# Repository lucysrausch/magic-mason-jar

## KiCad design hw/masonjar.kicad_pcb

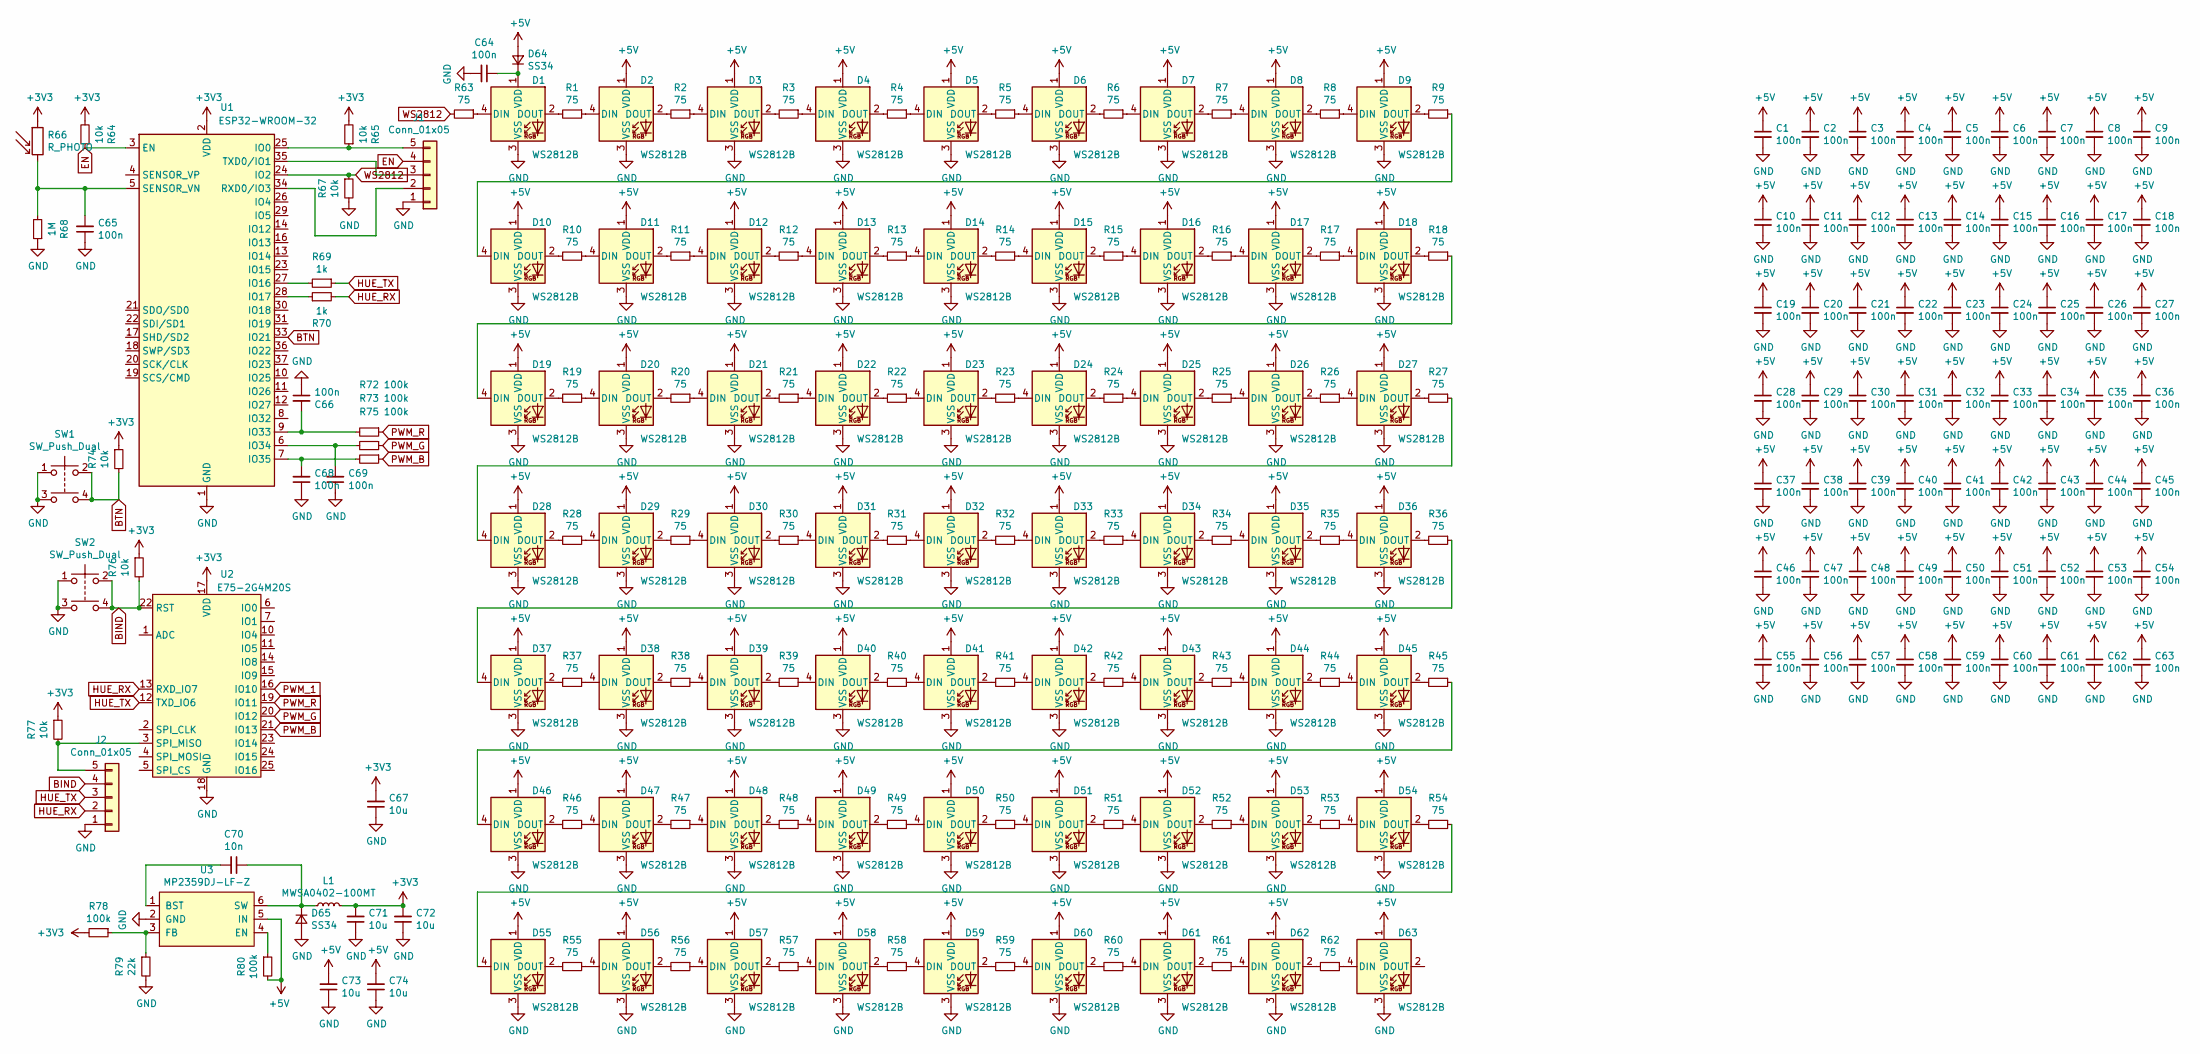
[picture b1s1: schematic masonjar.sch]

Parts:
C1, C2, C3, C4, C5, C6, C7, C8, C9, C10, C11, C12, C13, C14, C15, C16, C17, C18, C19, C20, C21, C22, C23, C24, C25, C26, C27, C28, C29, C30, C31, C32, C33, C34, C35, C36, C37, C38, C39, C40, C41, C42, C43, C44, C45, C46, C47, C48, C49, C50, C51, C52, C53, C54, C55, C56, C57, C58, C59, C60, C61, C62, C63, C64, C65, C66, C68, C69: 100n; C_0402_1005Metric
C67, C71, C72, C73, C74: 10u; C_0805_2012Metric
C70: 10n; C_0603_1608Metric
D1, D2, D3, D4, D5, D6, D7, D8, D9, D10, D11, D12, D13, D14, D15, D16, D17, D18, D19, D20, D21, D22, D23, D24, D25, D26, D27, D28, D29, D30, D31, D32, D33, D34, D35, D36, D37, D38, D39, D40, D41, D42, D43, D44, D45, D46, D47, D48, D49, D50, D51, D52, D53, D54, D55, D56, D57, D58, D59, D60, D61, D62, D63: WS2812B; WS2812D
D64, D65: SS34; D_SMA
J1, J2: Conn_01x05; PinHeader_1x05_P2.54mm_Vertical
L1: MWSA0402-100MT; L_Taiyo-Yuden_MD-4040
R1, R2, R3, R4, R5, R6, R7, R8, R9, R10, R11, R12, R13, R14, R15, R16, R17, R18, R19, R20, R21, R22, R23, R24, R25, R26, R27, R28, R29, R30, R31, R32, R33, R34, R35, R36, R37, R38, R39, R40, R41, R42, R43, R44, R45, R46, R47, R48, R49, R50, R51, R52, R53, R54, R55, R56, R57, R58, R59, R60, R61, R62, R63: 75; R_0402_1005Metric
R64, R65, R67, R74, R76, R77: 10k; R_0402_1005Metric
R66: R_PHOTO; LED_0805_2012Metric
R68: 1M; R_0402_1005Metric
R69, R70: 1k; R_0402_1005Metric
R72, R73, R75, R78, R80: 100k; R_0402_1005Metric
R79: 22k; R_0402_1005Metric
SW1, SW2: SW_Push_Dual; SW_Push_1P1T_NO_6x6mm_H9.5mm
U1: ESP32-WROOM-32
U2: E75-2G4M20S; E75-2G4M10S
U3: MP2359DJ-LF-Z_[C14259]; SOT-23-6

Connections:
+3V3: C67.2, C71.2, C72.2, L1.2, R64.2, R65.2, R66.1, R74.1, R76.1, R77.1, R78.2, U1.2 (VDD), U2.17 (VDD)
+5V: C1.1, C2.1, C3.1, C4.1, C5.1, C6.1, C7.1, C8.1, C9.1, C10.1, C11.1, C12.1, C13.1, C14.1, C15.1, C16.1, C17.1, C18.1, C19.1, C20.1, C21.1, C22.1, C23.1, C24.1, C25.1, C26.1, C27.1, C28.1, C29.1, C30.1, C31.1, C32.1, C33.1, C34.1, C35.1, C36.1, C37.1, C38.1, C39.1, C40.1, C41.1, C42.1, C43.1, C44.1, C45.1, C46.1, C47.1, C48.1, C49.1, C50.1, C51.1, C52.1, C53.1, C54.1, C55.1, C56.1, C57.1, C58.1, C59.1, C60.1, C61.1, C62.1, C63.1, C73.2, C74.2, D2.1 (VDD), D3.1 (VDD), D4.1 (VDD), D5.1 (VDD), D6.1 (VDD), D7.1 (VDD), D8.1 (VDD), D9.1 (VDD), D10.1 (VDD), D11.1 (VDD), D12.1 (VDD), D13.1 (VDD), D14.1 (VDD), D15.1 (VDD), D16.1 (VDD), D17.1 (VDD), D18.1 (VDD), D19.1 (VDD), D20.1 (VDD), D21.1 (VDD), D22.1 (VDD), D23.1 (VDD), D24.1 (VDD), D25.1 (VDD), D26.1 (VDD), D27.1 (VDD), D28.1 (VDD), D29.1 (VDD), D30.1 (VDD), D31.1 (VDD), D32.1 (VDD), D33.1 (VDD), D34.1 (VDD), D35.1 (VDD), D36.1 (VDD), D37.1 (VDD), D38.1 (VDD), D39.1 (VDD), D40.1 (VDD), D41.1 (VDD), D42.1 (VDD), D43.1 (VDD), D44.1 (VDD), D45.1 (VDD), D46.1 (VDD), D47.1 (VDD), D48.1 (VDD), D49.1 (VDD), D50.1 (VDD), D51.1 (VDD), D52.1 (VDD), D53.1 (VDD), D54.1 (VDD), D55.1 (VDD), D56.1 (VDD), D57.1 (VDD), D58.1 (VDD), D59.1 (VDD), D60.1 (VDD), D61.1 (VDD), D62.1 (VDD), D63.1 (VDD), D64.2 (A), R80.2, U3.5 (IN)
BIND: J2.4, R76.2, SW2.2, SW2.4, U2.22 (RST)
BTN: R74.2, SW1.2, SW1.4, U1.33 (IO21)
EN: J1.4, R64.1, U1.3 (EN)
GND: C1.2, C2.2, C3.2, C4.2, C5.2, C6.2, C7.2, C8.2, C9.2, C10.2, C11.2, C12.2, C13.2, C14.2, C15.2, C16.2, C17.2, C18.2, C19.2, C20.2, C21.2, C22.2, C23.2, C24.2, C25.2, C26.2, C27.2, C28.2, C29.2, C30.2, C31.2, C32.2, C33.2, C34.2, C35.2, C36.2, C37.2, C38.2, C39.2, C40.2, C41.2, C42.2, C43.2, C44.2, C45.2, C46.2, C47.2, C48.2, C49.2, C50.2, C51.2, C52.2, C53.2, C54.2, C55.2, C56.2, C57.2, C58.2, C59.2, C60.2, C61.2, C62.2, C63.2, C64.2, C65.1, C66.1, C67.1, C68.1, C69.1, C71.1, C72.1, C73.1, C74.1, D1.3 (VSS), D2.3 (VSS), D3.3 (VSS), D4.3 (VSS), D5.3 (VSS), D6.3 (VSS), D7.3 (VSS), D8.3 (VSS), D9.3 (VSS), D10.3 (VSS), D11.3 (VSS), D12.3 (VSS), D13.3 (VSS), D14.3 (VSS), D15.3 (VSS), D16.3 (VSS), D17.3 (VSS), D18.3 (VSS), D19.3 (VSS), D20.3 (VSS), D21.3 (VSS), D22.3 (VSS), D23.3 (VSS), D24.3 (VSS), D25.3 (VSS), D26.3 (VSS), D27.3 (VSS), D28.3 (VSS), D29.3 (VSS), D30.3 (VSS), D31.3 (VSS), D32.3 (VSS), D33.3 (VSS), D34.3 (VSS), D35.3 (VSS), D36.3 (VSS), D37.3 (VSS), D38.3 (VSS), D39.3 (VSS), D40.3 (VSS), D41.3 (VSS), D42.3 (VSS), D43.3 (VSS), D44.3 (VSS), D45.3 (VSS), D46.3 (VSS), D47.3 (VSS), D48.3 (VSS), D49.3 (VSS), D50.3 (VSS), D51.3 (VSS), D52.3 (VSS), D53.3 (VSS), D54.3 (VSS), D55.3 (VSS), D56.3 (VSS), D57.3 (VSS), D58.3 (VSS), D59.3 (VSS), D60.3 (VSS), D61.3 (VSS), D62.3 (VSS), D63.3 (VSS), D65.2 (A), J1.1, J2.1, R67.2, R68.1, R79.2, SW1.1, SW1.3, SW2.1, SW2.3, U1.1 (GND), U1.15 (GND), U1.38 (GND), U1.39, U2.18 (GND), U3.2 (GND)
HUE_RX: J2.2, R70.2, U2.13 (RXD_IO7)
HUE_TX: J2.3, R69.1, U2.12 (TXD_IO6)
unnamed: C64.1, D1.1 (VDD), D64.1 (K)
unnamed: C65.2, R66.2, R68.2, U1.5 (SENSOR_VN)
unnamed: C66.2, R72.2, U1.9 (IO33)
unnamed: C68.2, R75.2, U1.7 (IO35)
unnamed: C69.2, R73.2, U1.6 (IO34)
unnamed: C70.1, D65.1 (K), L1.1, U3.6 (SW)
unnamed: C70.2, U3.1 (BST)
unnamed: D1.2 (DOUT), R1.2
unnamed: D1.4 (DIN), R63.1
unnamed: D2.2 (DOUT), R2.2
unnamed: D2.4 (DIN), R1.1
unnamed: D3.2 (DOUT), R3.2
unnamed: D3.4 (DIN), R2.1
unnamed: D4.2 (DOUT), R4.2
unnamed: D4.4 (DIN), R3.1
unnamed: D5.2 (DOUT), R5.2
unnamed: D5.4 (DIN), R4.1
unnamed: D6.2 (DOUT), R6.2
unnamed: D6.4 (DIN), R5.1
unnamed: D7.2 (DOUT), R7.2
unnamed: D7.4 (DIN), R6.1
unnamed: D8.2 (DOUT), R8.2
unnamed: D8.4 (DIN), R7.1
unnamed: D9.2 (DOUT), R9.2
unnamed: D9.4 (DIN), R8.1
unnamed: D10.2 (DOUT), R10.2
unnamed: D10.4 (DIN), R9.1
unnamed: D11.2 (DOUT), R11.2
unnamed: D11.4 (DIN), R10.1
unnamed: D12.2 (DOUT), R12.2
unnamed: D12.4 (DIN), R11.1
unnamed: D13.2 (DOUT), R13.2
unnamed: D13.4 (DIN), R12.1
unnamed: D14.2 (DOUT), R14.2
unnamed: D14.4 (DIN), R13.1
unnamed: D15.2 (DOUT), R15.2
unnamed: D15.4 (DIN), R14.1
unnamed: D16.2 (DOUT), R16.2
unnamed: D16.4 (DIN), R15.1
unnamed: D17.2 (DOUT), R17.2
unnamed: D17.4 (DIN), R16.1
unnamed: D18.2 (DOUT), R18.2
unnamed: D18.4 (DIN), R17.1
unnamed: D19.2 (DOUT), R19.2
unnamed: D19.4 (DIN), R18.1
unnamed: D20.2 (DOUT), R20.2
unnamed: D20.4 (DIN), R19.1
unnamed: D21.2 (DOUT), R21.2
unnamed: D21.4 (DIN), R20.1
unnamed: D22.2 (DOUT), R22.2
unnamed: D22.4 (DIN), R21.1
unnamed: D23.2 (DOUT), R23.2
unnamed: D23.4 (DIN), R22.1
unnamed: D24.2 (DOUT), R24.2
unnamed: D24.4 (DIN), R23.1
unnamed: D25.2 (DOUT), R25.2
unnamed: D25.4 (DIN), R24.1
unnamed: D26.2 (DOUT), R26.2
unnamed: D26.4 (DIN), R25.1
unnamed: D27.2 (DOUT), R27.2
unnamed: D27.4 (DIN), R26.1
unnamed: D28.2 (DOUT), R28.2
unnamed: D28.4 (DIN), R27.1
unnamed: D29.2 (DOUT), R29.2
unnamed: D29.4 (DIN), R28.1
unnamed: D30.2 (DOUT), R30.2
unnamed: D30.4 (DIN), R29.1
unnamed: D31.2 (DOUT), R31.2
unnamed: D31.4 (DIN), R30.1
unnamed: D32.2 (DOUT), R32.2
unnamed: D32.4 (DIN), R31.1
unnamed: D33.2 (DOUT), R33.2
unnamed: D33.4 (DIN), R32.1
unnamed: D34.2 (DOUT), R34.2
unnamed: D34.4 (DIN), R33.1
unnamed: D35.2 (DOUT), R35.2
unnamed: D35.4 (DIN), R34.1
unnamed: D36.2 (DOUT), R36.2
unnamed: D36.4 (DIN), R35.1
unnamed: D37.2 (DOUT), R37.2
unnamed: D37.4 (DIN), R36.1
unnamed: D38.2 (DOUT), R38.2
unnamed: D38.4 (DIN), R37.1
unnamed: D39.2 (DOUT), R39.2
unnamed: D39.4 (DIN), R38.1
unnamed: D40.2 (DOUT), R40.2
unnamed: D40.4 (DIN), R39.1
unnamed: D41.2 (DOUT), R41.2
unnamed: D41.4 (DIN), R40.1
unnamed: D42.2 (DOUT), R42.2
unnamed: D42.4 (DIN), R41.1
unnamed: D43.2 (DOUT), R43.2
unnamed: D43.4 (DIN), R42.1
unnamed: D44.2 (DOUT), R44.2
unnamed: D44.4 (DIN), R43.1
unnamed: D45.2 (DOUT), R45.2
unnamed: D45.4 (DIN), R44.1
unnamed: D46.2 (DOUT), R46.2
unnamed: D46.4 (DIN), R45.1
unnamed: D47.2 (DOUT), R47.2
unnamed: D47.4 (DIN), R46.1
unnamed: D48.2 (DOUT), R48.2
unnamed: D48.4 (DIN), R47.1
unnamed: D49.2 (DOUT), R49.2
unnamed: D49.4 (DIN), R48.1
unnamed: D50.2 (DOUT), R50.2
unnamed: D50.4 (DIN), R49.1
unnamed: D51.2 (DOUT), R51.2
unnamed: D51.4 (DIN), R50.1
unnamed: D52.2 (DOUT), R52.2
unnamed: D52.4 (DIN), R51.1
unnamed: D53.2 (DOUT), R53.2
unnamed: D53.4 (DIN), R52.1
unnamed: D54.2 (DOUT), R54.2
unnamed: D54.4 (DIN), R53.1
unnamed: D55.2 (DOUT), R55.2
unnamed: D55.4 (DIN), R54.1
unnamed: D56.2 (DOUT), R56.2
unnamed: D56.4 (DIN), R55.1
unnamed: D57.2 (DOUT), R57.2
unnamed: D57.4 (DIN), R56.1
unnamed: D58.2 (DOUT), R58.2
unnamed: D58.4 (DIN), R57.1
unnamed: D59.2 (DOUT), R59.2
unnamed: D59.4 (DIN), R58.1
unnamed: D60.2 (DOUT), R60.2
unnamed: D60.4 (DIN), R59.1
unnamed: D61.2 (DOUT), R61.2
unnamed: D61.4 (DIN), R60.1
unnamed: D62.2 (DOUT), R62.2
unnamed: D62.4 (DIN), R61.1
unnamed: D63.4 (DIN), R62.1
unnamed: J1.2, U1.34 (RXD0/IO3)
unnamed: J1.3, U1.35 (TXD0/IO1)
unnamed: J1.5, R65.1, U1.25 (IO0)
unnamed: J2.5, R77.2, U2.3 (SPI_MISO)
unnamed: R69.2, U1.27 (IO16)
unnamed: R70.1, U1.28 (IO17)
unnamed: R78.1, R79.1, U3.3 (FB)
unnamed: R80.1, U3.4 (EN)
PWM_1: U2.16 (IO10)
PWM_B: R75.1, U2.21 (IO13)
PWM_G: R73.1, U2.20 (IO12)
PWM_R: R72.1, U2.19 (IO11)
WS2812: R63.2, R67.1, U1.24 (IO2)

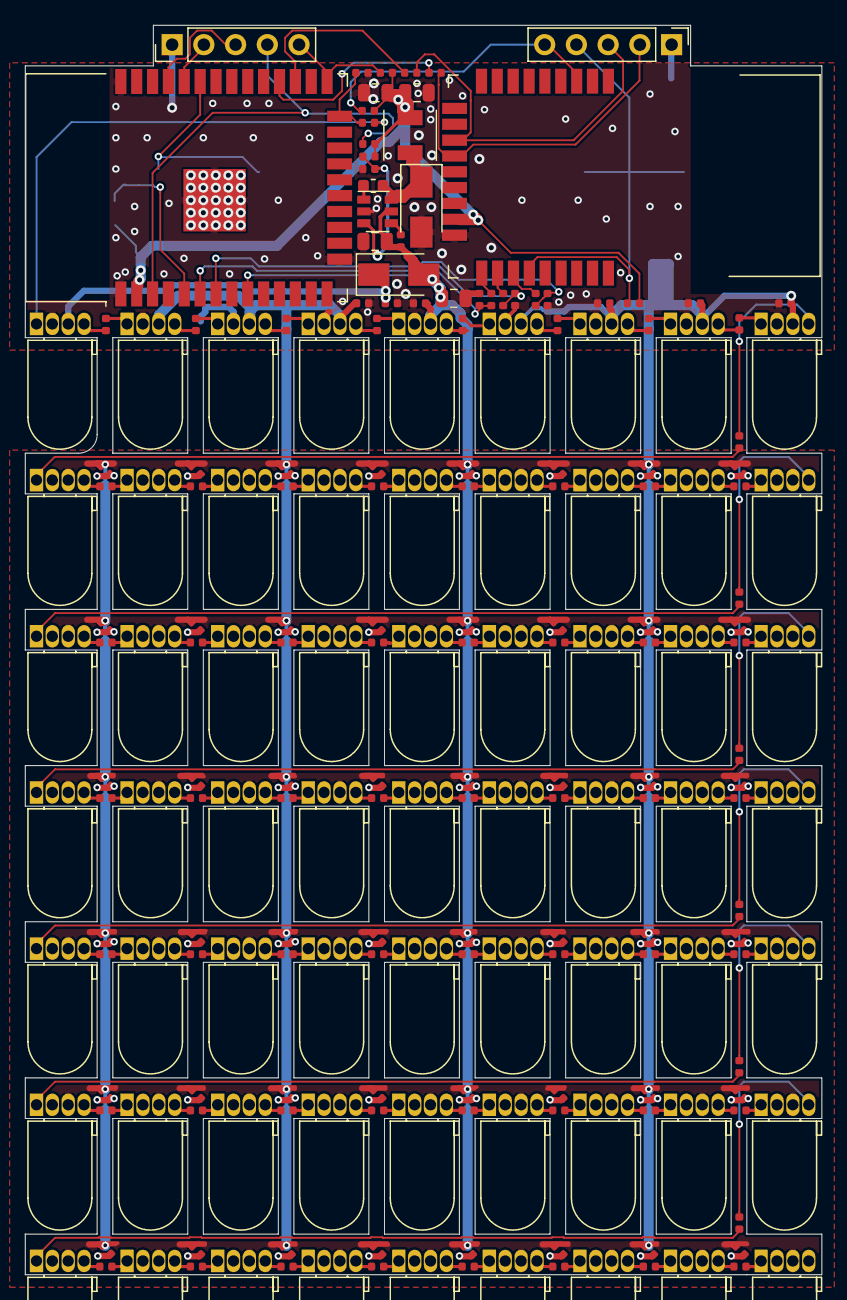
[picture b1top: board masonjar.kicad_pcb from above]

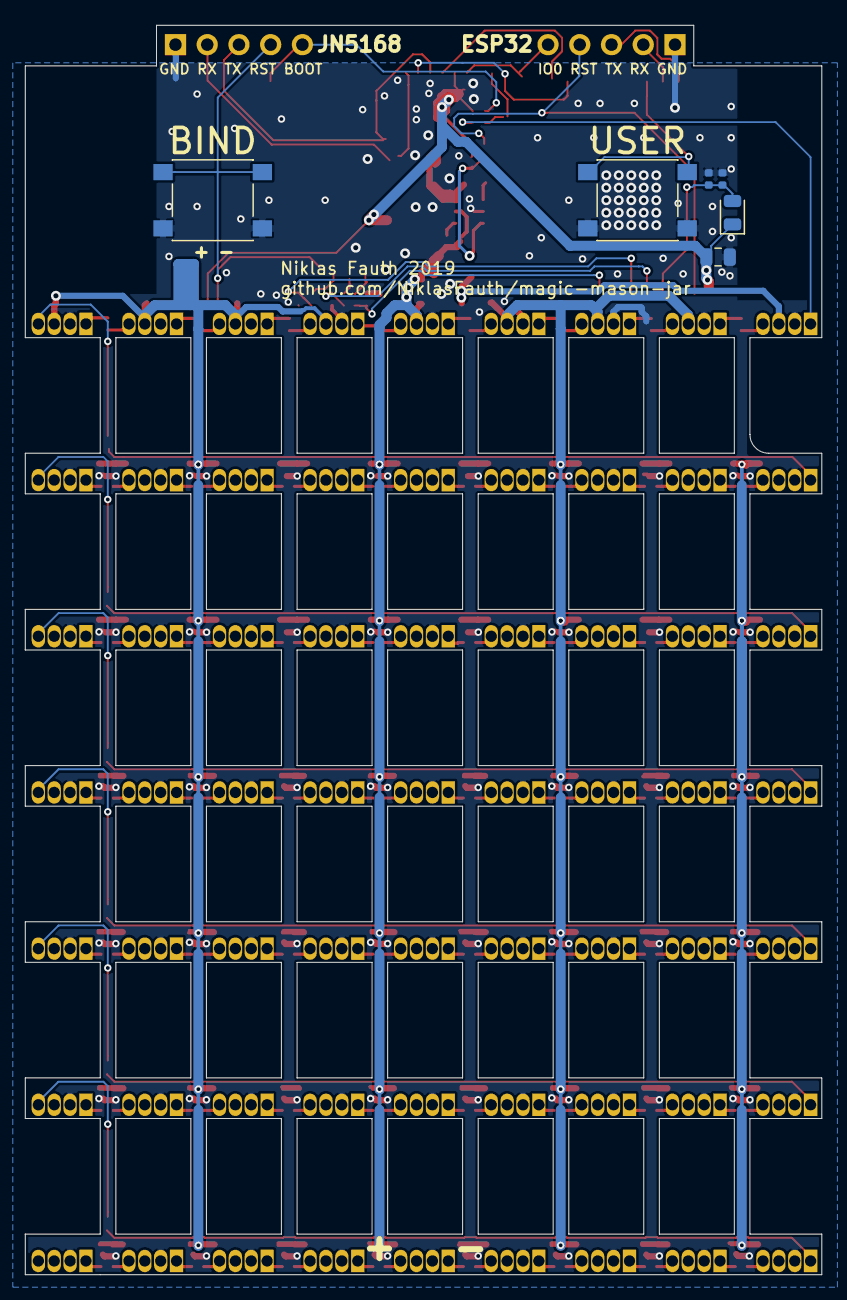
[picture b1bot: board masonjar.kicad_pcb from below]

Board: 2 copper layers, 63.8 x 100.0 mm, 215 parts (6 on the bottom side), 152 nets.

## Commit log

2019-12-22 added gitignore
2019-12-22 working on layout
2020-01-18 first fire animation with hue integration
